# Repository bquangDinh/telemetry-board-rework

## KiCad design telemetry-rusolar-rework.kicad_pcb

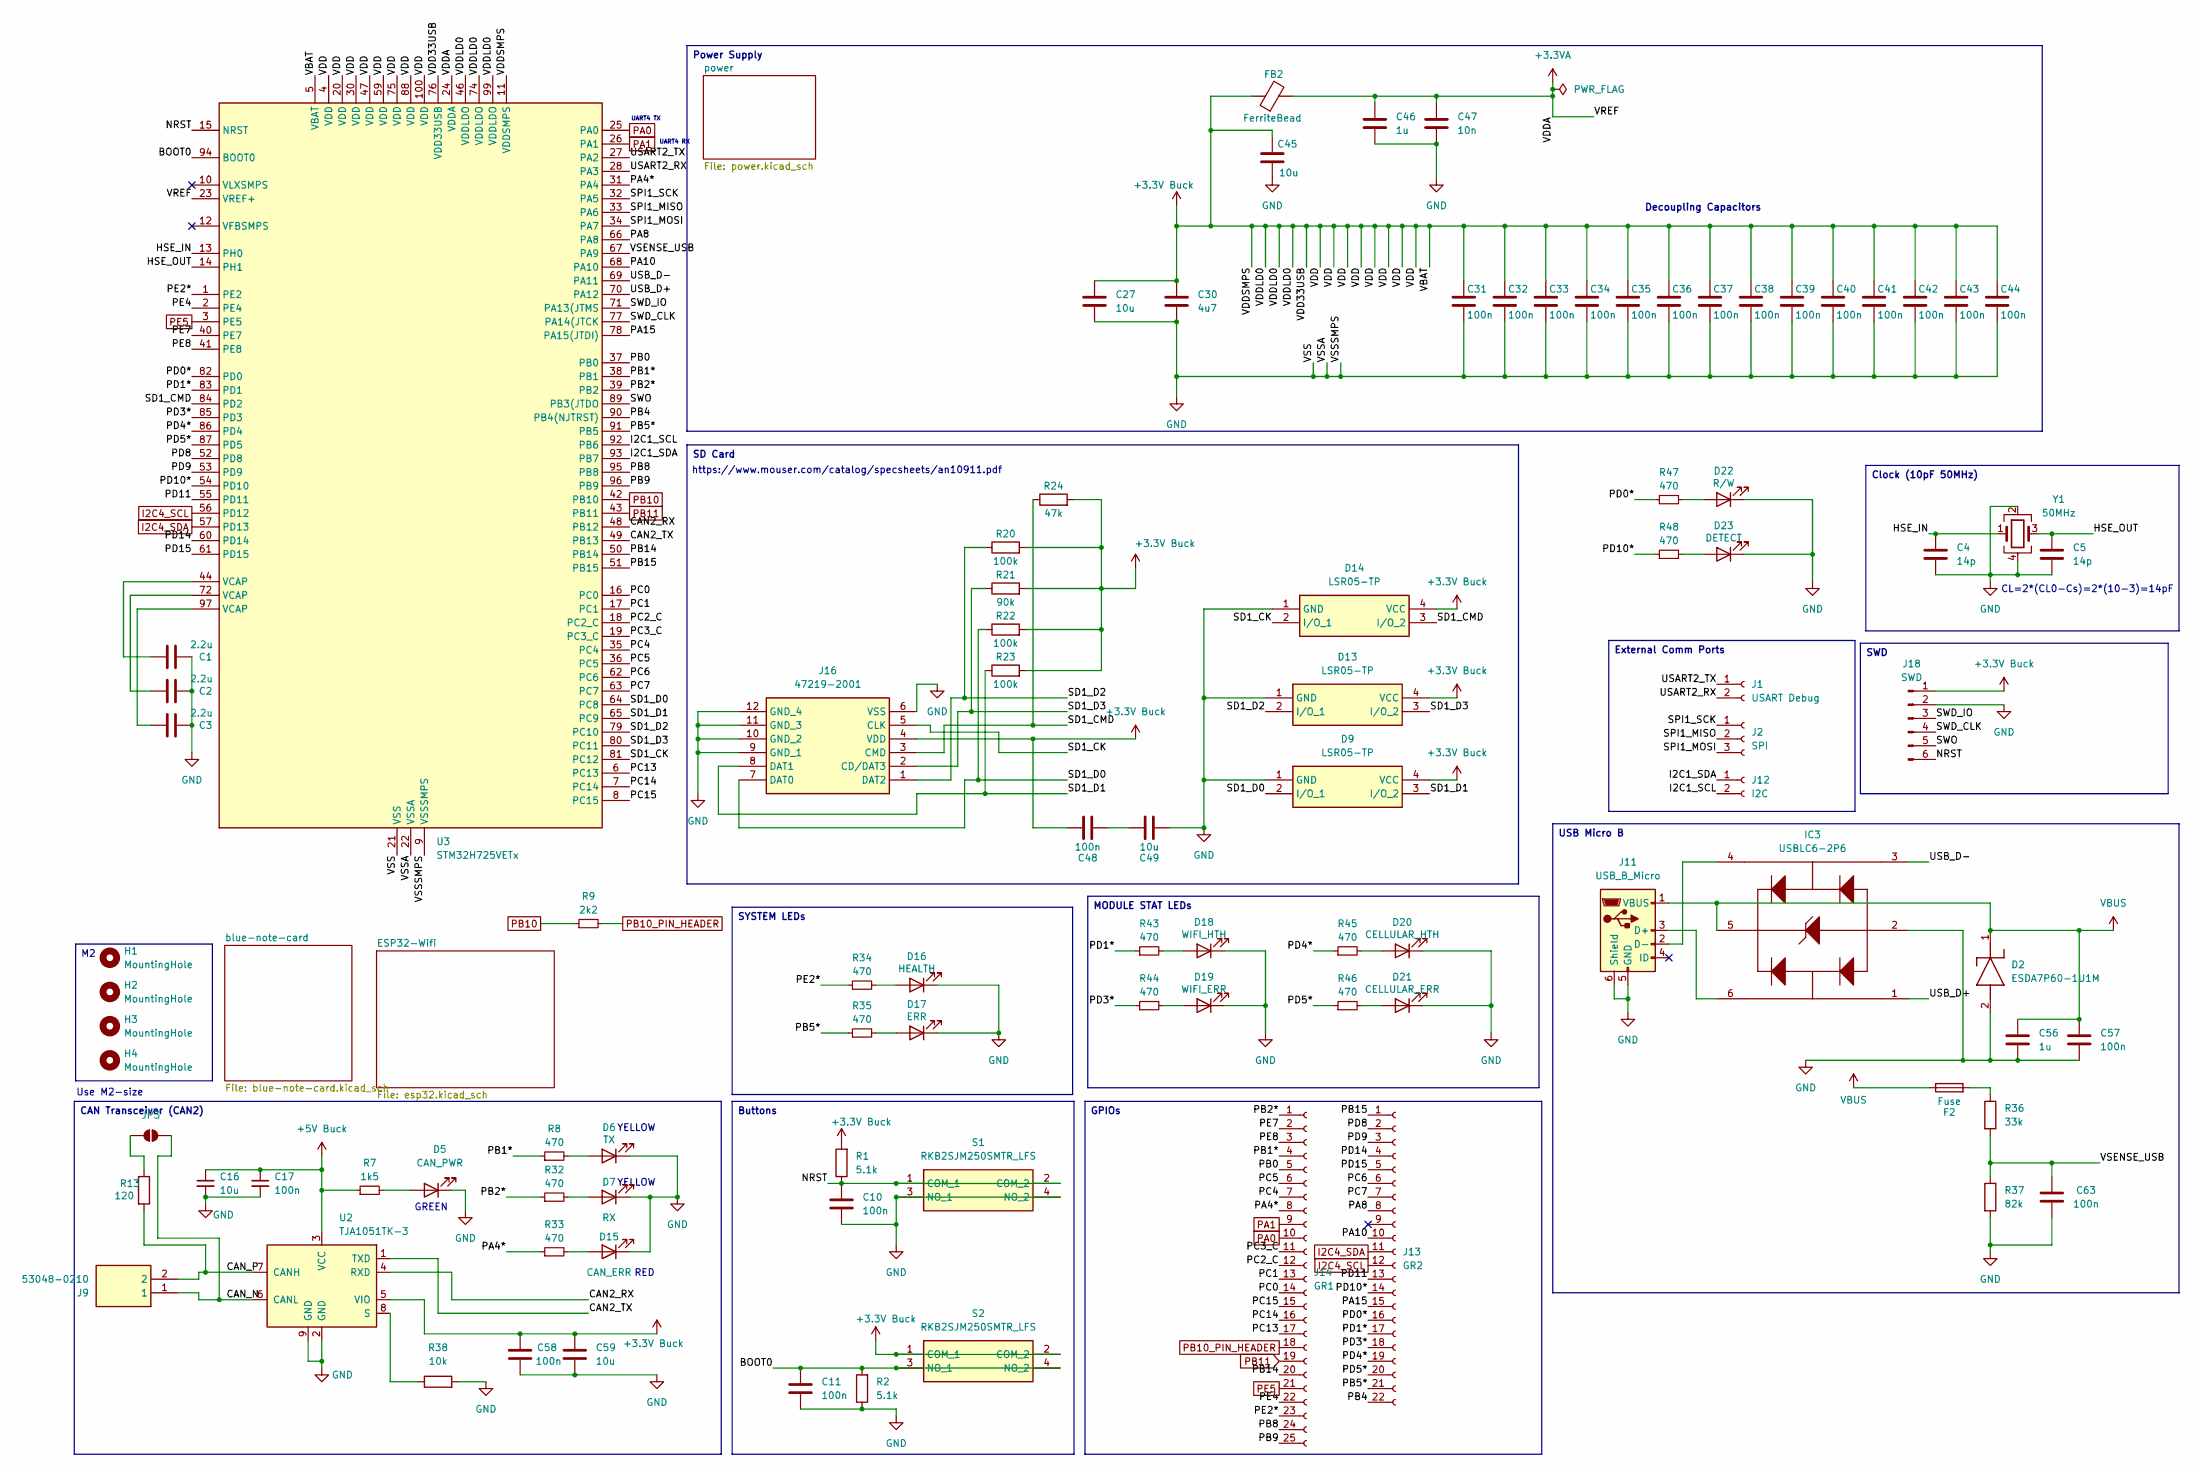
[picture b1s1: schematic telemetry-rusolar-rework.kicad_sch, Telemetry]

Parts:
C1, C2, C3: 2.2u; C_0805_2012Metric_Pad1.18x1.45mm_HandSolder
C4, C5: 14p; C_0603_1608Metric_Pad1.08x0.95mm_HandSolder
C10, C11, C17, C31, C32, C33, C34, C35, C36, C37, C38, C39, C40, C41, C42, C43, C44, C48, C57, C58, C63: 100n; C_0603_1608Metric_Pad1.08x0.95mm_HandSolder
C16, C27, C45, C49, C59: 10u; C_0805_2012Metric_Pad1.18x1.45mm_HandSolder
C30: 4u7; C_0805_2012Metric_Pad1.18x1.45mm_HandSolder
C46, C56: 1u; C_0805_2012Metric_Pad1.18x1.45mm_HandSolder
C47: 10n; C_0603_1608Metric_Pad1.08x0.95mm_HandSolder
D2: ESDA7P60-1U1M; ESDA7P601U1M; Mouser Part Number 511-ESDA7P60-1U1M
D5: CAN_PWR; LED_0805_2012Metric_Pad1.15x1.40mm_HandSolder
D6: TX; LED_0805_2012Metric_Pad1.15x1.40mm_HandSolder
D7: RX; LED_0805_2012Metric_Pad1.15x1.40mm_HandSolder
D9, D13, D14: LSR05-TP; LSR05TP; Mouser Part Number 833-LSR05-TP
D15: CAN_ERR; LED_0805_2012Metric_Pad1.15x1.40mm_HandSolder
D16: HEALTH; LED_0805_2012Metric_Pad1.15x1.40mm_HandSolder
D17: ERR; LED_0805_2012Metric_Pad1.15x1.40mm_HandSolder
D18: WIFI_HTH; LED_0805_2012Metric_Pad1.15x1.40mm_HandSolder
D19: WIFI_ERR; LED_0805_2012Metric_Pad1.15x1.40mm_HandSolder
D20: CELLULAR_HTH; LED_0805_2012Metric_Pad1.15x1.40mm_HandSolder
D21: CELLULAR_ERR; LED_0805_2012Metric_Pad1.15x1.40mm_HandSolder
D22: R/W; LED_0805_2012Metric_Pad1.15x1.40mm_HandSolder
D23: DETECT; LED_0805_2012Metric_Pad1.15x1.40mm_HandSolder
F2: Fuse; Fuse_0603_1608Metric_Pad1.05x0.95mm_HandSolder
FB2: FerriteBead; L_0805_2012Metric_Pad1.15x1.40mm_HandSolder
H1, H2, H3, H4: MountingHole; MountingHole_2.2mm_M2
IC3: USBLC6-2P6; USBLC62P6; Mouser Part Number 511-USBLC6-2P6
J1: USART Debug; PinHeader_1x02_P2.00mm_Vertical
J2: SPI; PinHeader_1x03_P2.00mm_Vertical
J9: 53048-0210; SHDRRA2W35P0X125_1X2_425X550X350P; Mouser Part Number 538-53048-0210
J11: USB_B_Micro; USB_Micro-B_Wuerth_629105150521
J12: I2C; PinHeader_1x02_P2.00mm_Vertical
J13: GR2; PinSocket_1x22_P2.00mm_Vertical
J14: GR1; PinSocket_1x25_P2.00mm_Vertical
J16: 47219-2001; 472192001; Mouser Part Number 538-47219-2001
J18: SWD; PinHeader_1x06_P2.00mm_Vertical
JP3: SolderJumper_2_Open; SolderJumper-2_P1.3mm_Open_RoundedPad1.0x1.5mm
R1, R2: 5.1k; R_0603_1608Metric_Pad0.98x0.95mm_HandSolder
R7: 1k5; R_0603_1608Metric_Pad0.98x0.95mm_HandSolder
R8, R32, R33, R34, R35, R43, R44, R45, R46, R47, R48: 470; R_0603_1608Metric_Pad0.98x0.95mm_HandSolder
R9: 2k2; R_0603_1608Metric_Pad0.98x0.95mm_HandSolder
R13: 120; R_0603_1608Metric_Pad0.98x0.95mm_HandSolder
R20, R22, R23: 100k; R_0805_2012Metric_Pad1.20x1.40mm_HandSolder
R21: 90k; R_0805_2012Metric_Pad1.20x1.40mm_HandSolder
R24: 47k; R_0805_2012Metric_Pad1.20x1.40mm_HandSolder
R36: 33k; R_0603_1608Metric_Pad0.98x0.95mm_HandSolder
R37: 82k; R_0603_1608Metric_Pad0.98x0.95mm_HandSolder
R38: 10k; R_0603_1608Metric_Pad0.98x0.95mm_HandSolder
S1, S2: RKB2SJM250SMTR_LFS; RKB2SJM250SMTRLFS; Mouser Part Number 611-RKB2SJM250SMTRLF
U2: TJA1051TK-3; DFN-8-1EP_3x3mm_P0.65mm_EP1.55x2.4mm
U3: STM32H725VETx; LQFP-100_14x14mm_P0.5mm
Y1: 50MHz; Crystal_SMD_3225-4Pin_3.2x2.5mm

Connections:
+3.3V Buck: C27.2, C30.2, C31.1, C32.1, C33.1, C34.1, C35.1, C36.1, C37.1, C38.1, C39.1, C40.1, C41.1, C42.1, C43.1, C44.1, C45.2, C48.1, C58.2, C59.2, D9.4 (VCC), D13.4 (VCC), D14.4 (VCC), FB2.1, J16.4 (VDD), J18.1, R1.2, R20.2, R21.2, R22.2, R23.2, R24.2, S2.1 (COM_1), S2.2 (COM_2), U2.5 (VIO), U3.4 (VDD), U3.5 (VBAT), U3.11 (VDDSMPS), U3.20 (VDD), U3.30 (VDD), U3.46 (VDDLDO), U3.47 (VDD), U3.59 (VDD), U3.74 (VDDLDO), U3.75 (VDD), U3.76 (VDD33USB), U3.88 (VDD), U3.99 (VDDLDO), U3.100 (VDD); also elsewhere on the board
+3.3VA: C46.2, C47.2, FB2.2, U3.23 (VREF+), U3.24 (VDDA)
+5V Buck: C16.1, C17.1, R7.1, U2.3 (VCC); also elsewhere on the board
/BOOT0: C11.1, R2.2, S2.3 (NO_1), S2.4 (NO_2), U3.94 (BOOT0)
/CAN2_RX: U2.4 (RXD), U3.48 (PB12)
/CAN2_TX: U2.1 (TXD), U3.49 (PB13)
/CAN_N: J9.1, JP3.2 (B), U2.6 (CANL)
/CAN_P: J9.2, R13.2, U2.7 (CANH)
/HSE_IN: C4.1, U3.13 (PH0), Y1.1
/HSE_OUT: C5.1, U3.14 (PH1), Y1.3
/I2C1_SCL: J12.2, U3.92 (PB6)
/I2C1_SDA: J12.1, U3.93 (PB7)
/NRST: C10.1, J18.6, R1.1, S1.1 (COM_1), S1.2 (COM_2), U3.15 (NRST)
/PA4*: J14.8, R33.1, U3.31 (PA4)
/PA8: J13.8, U3.66 (PA8)
/PA10: J13.10, U3.68 (PA10)
/PA15: J13.15, U3.78 (PA15(JTDI))
/PB0: J14.5, U3.37 (PB0)
/PB1*: J14.4, R8.1, U3.38 (PB1)
/PB2*: J14.1, R32.1, U3.39 (PB2)
/PB4: J13.22, U3.90 (PB4(NJTRST))
/PB5*: J13.21, R35.1, U3.91 (PB5)
/PB8: J14.24, U3.95 (PB8)
/PB9: J14.25, U3.96 (PB9)
/PB14: J14.20, U3.50 (PB14)
/PB15: J13.1, U3.51 (PB15)
/PC0: J14.14, U3.16 (PC0)
/PC1: J14.13, U3.17 (PC1)
/PC2_C: J14.12, U3.18 (PC2_C)
/PC3_C: J14.11, U3.19 (PC3_C)
/PC4: J14.7, U3.35 (PC4)
/PC5: J14.6, U3.36 (PC5)
/PC6: J13.6, U3.62 (PC6)
/PC7: J13.7, U3.63 (PC7)
/PC13: J14.17, U3.6 (PC13)
/PC14: J14.16, U3.7 (PC14)
/PC15: J14.15, U3.8 (PC15)
/PD0*: J13.16, R47.1, U3.82 (PD0)
/PD1*: J13.17, R43.1, U3.83 (PD1)
/PD3*: J13.18, R44.1, U3.85 (PD3)
/PD4*: J13.19, R45.1, U3.86 (PD4)
/PD5*: J13.20, R46.1, U3.87 (PD5)
/PD8: J13.2, U3.52 (PD8)
/PD9: J13.3, U3.53 (PD9)
/PD10*: J13.14, R48.1, U3.54 (PD10)
/PD11: J13.13, U3.55 (PD11)
/PD14: J13.4, U3.60 (PD14)
/PD15: J13.5, U3.61 (PD15)
/PE2*: J14.23, R34.1, U3.1 (PE2)
/PE4: J14.22, U3.2 (PE4)
/PE7: J14.2, U3.40 (PE7)
/PE8: J14.3, U3.41 (PE8)
/SD1_CK: D14.2 (I/O_1), J16.5 (CLK), U3.81 (PC12)
/SD1_CMD: D14.3 (I/O_2), J16.3 (CMD), R24.1, U3.84 (PD2)
/SD1_D0: D9.2 (I/O_1), J16.7 (DAT0), R22.1, U3.64 (PC8)
/SD1_D1: D9.3 (I/O_2), J16.8 (DAT1), R23.1, U3.65 (PC9)
/SD1_D2: D13.2 (I/O_1), J16.1 (DAT2), R20.1, U3.79 (PC10)
/SD1_D3: D13.3 (I/O_2), J16.2 (CD/DAT3), R21.1, U3.80 (PC11)
/SPI1_MISO: J2.2, U3.33 (PA6)
/SPI1_MOSI: J2.3, U3.34 (PA7)
/SPI1_SCK: J2.1, U3.32 (PA5)
/SWD_CLK: J18.4, U3.77 (PA14(JTCK)
/SWD_IO: J18.3, U3.71 (PA13(JTMS)
/SWO: J18.5, U3.89 (PB3(JTDO)
/USART2_RX: J1.2, U3.28 (PA3)
/USART2_TX: J1.1, U3.27 (PA2)
/USB_D+: IC3.1 (I/O1_1), U3.70 (PA12)
/USB_D-: IC3.3 (I/O2_1), U3.69 (PA11)
/VSENSE_USB: C63.1, R36.2, R37.1, U3.67 (PA9)
GND: C1.1, C2.1, C3.1, C4.2, C5.2, C10.2, C11.2, C16.2, C17.2, C27.1, C30.1, C31.2, C32.2, C33.2, C34.2, C35.2, C36.2, C37.2, C38.2, C39.2, C40.2, C41.2, C42.2, C43.2, C44.2, C45.1, C46.1, C47.1, C49.2, C56.2, C57.2, C58.1, C59.1, C63.2, D2.2 (A), D5.1 (K), D6.1 (K), D7.1 (K), D9.1 (GND), D13.1 (GND), D14.1 (GND), D15.1 (K), D16.1 (K), D17.1 (K), D18.1 (K), D19.1 (K), D20.1 (K), D21.1 (K), D22.1 (K), D23.1 (K), IC3.2 (GND), J11.5 (GND), J11.6 (Shield), J16.6 (VSS), J16.9 (GND_1), J16.10 (GND_2), J16.11 (GND_3), J16.12 (GND_4), J18.2, R2.1, R37.2, R38.2, S1.3 (NO_1), S1.4 (NO_2), U2.2 (GND), U2.9 (GND), U3.9 (VSSSMPS), U3.21 (VSS), U3.22 (VSSA), U3.29 (VSS), U3.45 (VSS), U3.58 (VSS), U3.73 (VSS), U3.98 (VSS), Y1.2, Y1.4; also elsewhere on the board
I2C4_SCL: J13.12, U3.56 (PD12); also elsewhere on the board
I2C4_SDA: J13.11, U3.57 (PD13); also elsewhere on the board
unnamed: C1.2, U3.44 (VCAP)
unnamed: C2.2, U3.72 (VCAP)
unnamed: C3.2, U3.97 (VCAP)
unnamed: C48.2, C49.1
unnamed: D5.2 (A), R7.2
unnamed: D6.2 (A), R8.2
unnamed: D7.2 (A), R32.2
unnamed: D15.2 (A), R33.2
unnamed: D16.2 (A), R34.2
unnamed: D17.2 (A), R35.2
unnamed: D18.2 (A), R43.2
unnamed: D19.2 (A), R44.2
unnamed: D20.2 (A), R45.2
unnamed: D21.2 (A), R46.2
unnamed: D22.2 (A), R47.2
unnamed: D23.2 (A), R48.2
unnamed: F2.2, R36.1
unnamed: IC3.6 (I/O1_2), J11.3 (D+)
unnamed: IC3.4 (I/O2_2), J11.2 (D-)
unnamed: JP3.1 (A), R13.1
unnamed: R38.1, U2.8 (S)
PA0: J14.10, U3.25 (PA0); also elsewhere on the board
PA1: J14.9, U3.26 (PA1); also elsewhere on the board
PB10: R9.1, U3.42 (PB10)
PB10_PIN_HEADER: J14.18, R9.2; also elsewhere on the board
PB11: J14.19, U3.43 (PB11); also elsewhere on the board
PE5: J14.21, U3.3 (PE5); also elsewhere on the board
VBUS: C56.1, C57.1, D2.1 (K), F2.1, IC3.5 (VBUS), J11.1 (VBUS)

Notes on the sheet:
RED
UART4 TX
https://www.mouser.com/catalog/specsheets/an10911.pdf
Use M2-size
GREEN
CL=2*(CL0-Cs)=2*(10-3)=14pF
UART4 RX
YELLOW
Decoupling Capacitors
SD Card
Buttons
SYSTEM LEDs
Clock (10pF 50MHz)
Power Supply
MODULE STAT LEDs
SWD
USB Micro B
GPIOs
CAN Transceiver (CAN2)
External Comm Ports

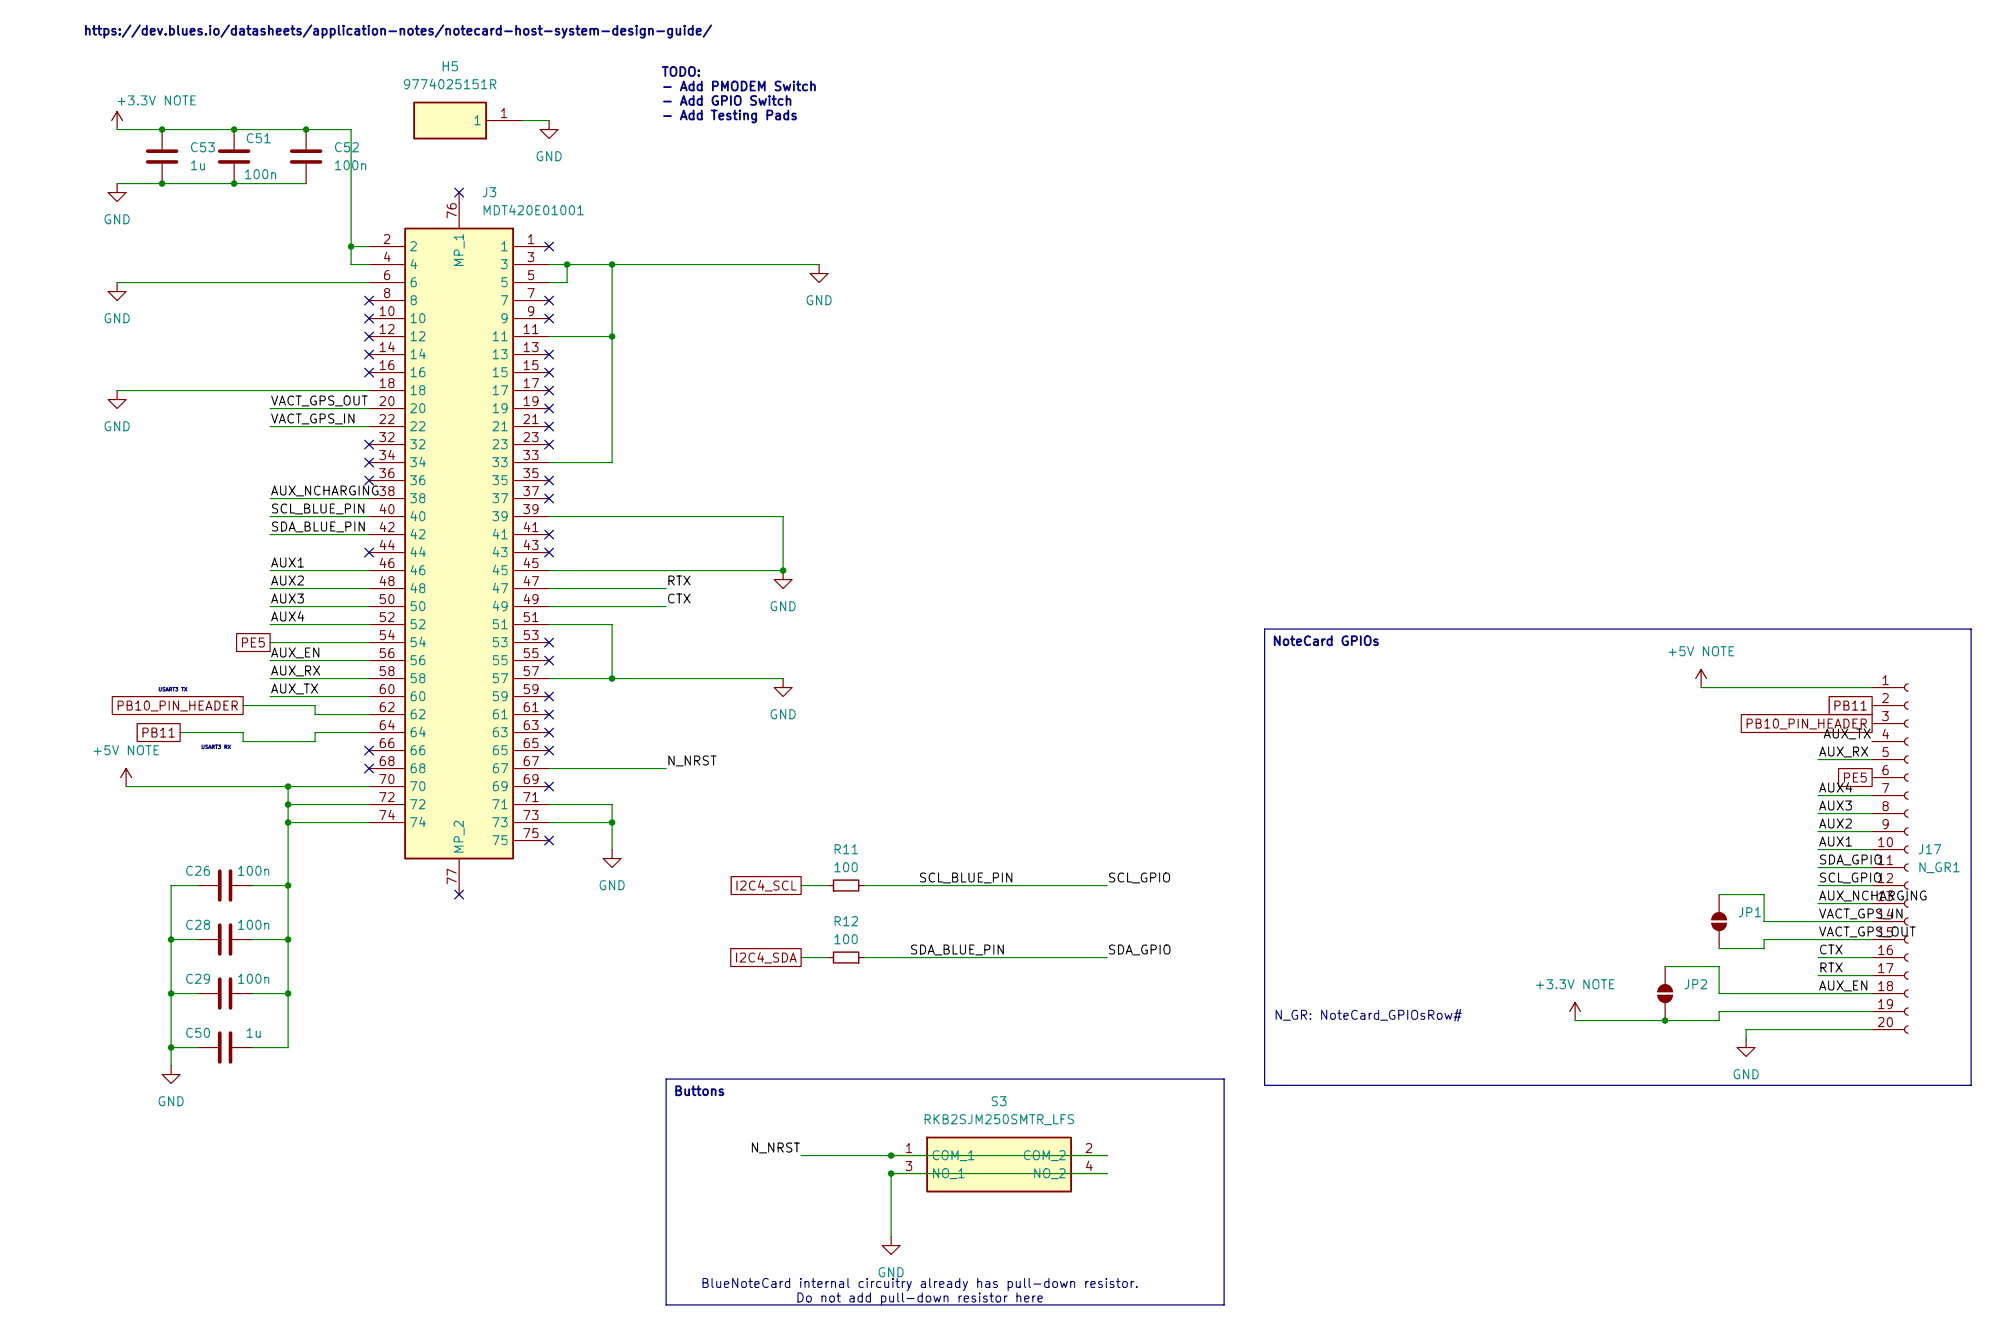
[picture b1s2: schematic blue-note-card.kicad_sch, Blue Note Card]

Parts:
C26, C28, C29, C51, C52: 100n; C_0603_1608Metric_Pad1.08x0.95mm_HandSolder
C50, C53: 1u; C_0805_2012Metric_Pad1.18x1.45mm_HandSolder
H5: 9774025151R; Mouser Part Number 710-9774025151R
J3: MDT420E01001; Mouser Part Number 523-MDT420E01001
J17: N_GR1; PinSocket_1x20_P2.00mm_Vertical
JP1, JP2: SolderJumper_2_Open; SolderJumper-2_P1.3mm_Open_RoundedPad1.0x1.5mm
R11, R12: 100; R_0603_1608Metric_Pad0.98x0.95mm_HandSolder
S3: RKB2SJM250SMTR_LFS; RKB2SJM250SMTRLFS; Mouser Part Number 611-RKB2SJM250SMTRLF

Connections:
+3.3V NOTE: C51.2, C52.2, C53.2, J3.2, J3.4, J17.19, JP2.2 (B); also elsewhere on the board
+5V NOTE: C26.2, C28.2, C29.2, C50.2, J3.70, J3.72, J3.74, J17.1; also elsewhere on the board
/blue-note-card/AUX1: J3.46, J17.10
/blue-note-card/AUX2: J3.48, J17.9
/blue-note-card/AUX3: J3.50, J17.8
/blue-note-card/AUX4: J3.52, J17.7
/blue-note-card/AUX_EN: J3.56, J17.18, JP2.1 (A)
/blue-note-card/AUX_NCHARGING: J3.38, J17.13
/blue-note-card/AUX_RX: J3.58, J17.5
/blue-note-card/AUX_TX: J3.60, J17.4
/blue-note-card/CTX: J3.49, J17.16
/blue-note-card/N_NRST: J3.67, S3.1 (COM_1), S3.2 (COM_2)
/blue-note-card/RTX: J3.47, J17.17
/blue-note-card/SCL_BLUE_PIN: J3.40, J17.12, R11.2
/blue-note-card/SDA_BLUE_PIN: J3.42, J17.11, R12.1
/blue-note-card/VACT_GPS_IN: J3.22, J17.14, JP1.1 (A)
/blue-note-card/VACT_GPS_OUT: J3.20, J17.15, JP1.2 (B)
GND: C26.1, C28.1, C29.1, C50.1, C51.1, C52.1, C53.1, H5.1, J3.3, J3.5, J3.6, J3.11, J3.18, J3.33, J3.39, J3.45, J3.51, J3.57, J3.71, J3.73, J17.20, S3.3 (NO_1), S3.4 (NO_2); also elsewhere on the board
I2C4_SCL: R11.1; also elsewhere on the board
I2C4_SDA: R12.2; also elsewhere on the board
PB10_PIN_HEADER: J3.62, J17.3; also elsewhere on the board
PB11: J3.64, J17.2; also elsewhere on the board
PE5: J3.54, J17.6; also elsewhere on the board

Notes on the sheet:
TODO: - Add PMODEM Switch - Add GPIO Switch - Add Testing Pads
BlueNoteCard internal circuitry already has pull-down resistor. Do not add pull-down resistor here
https://dev.blues.io/datasheets/application-notes/notecard-host-system-design-guide/
N_GR: NoteCard_GPIOsRow#
USART3 RX
USART3 TX
Buttons
NoteCard GPIOs

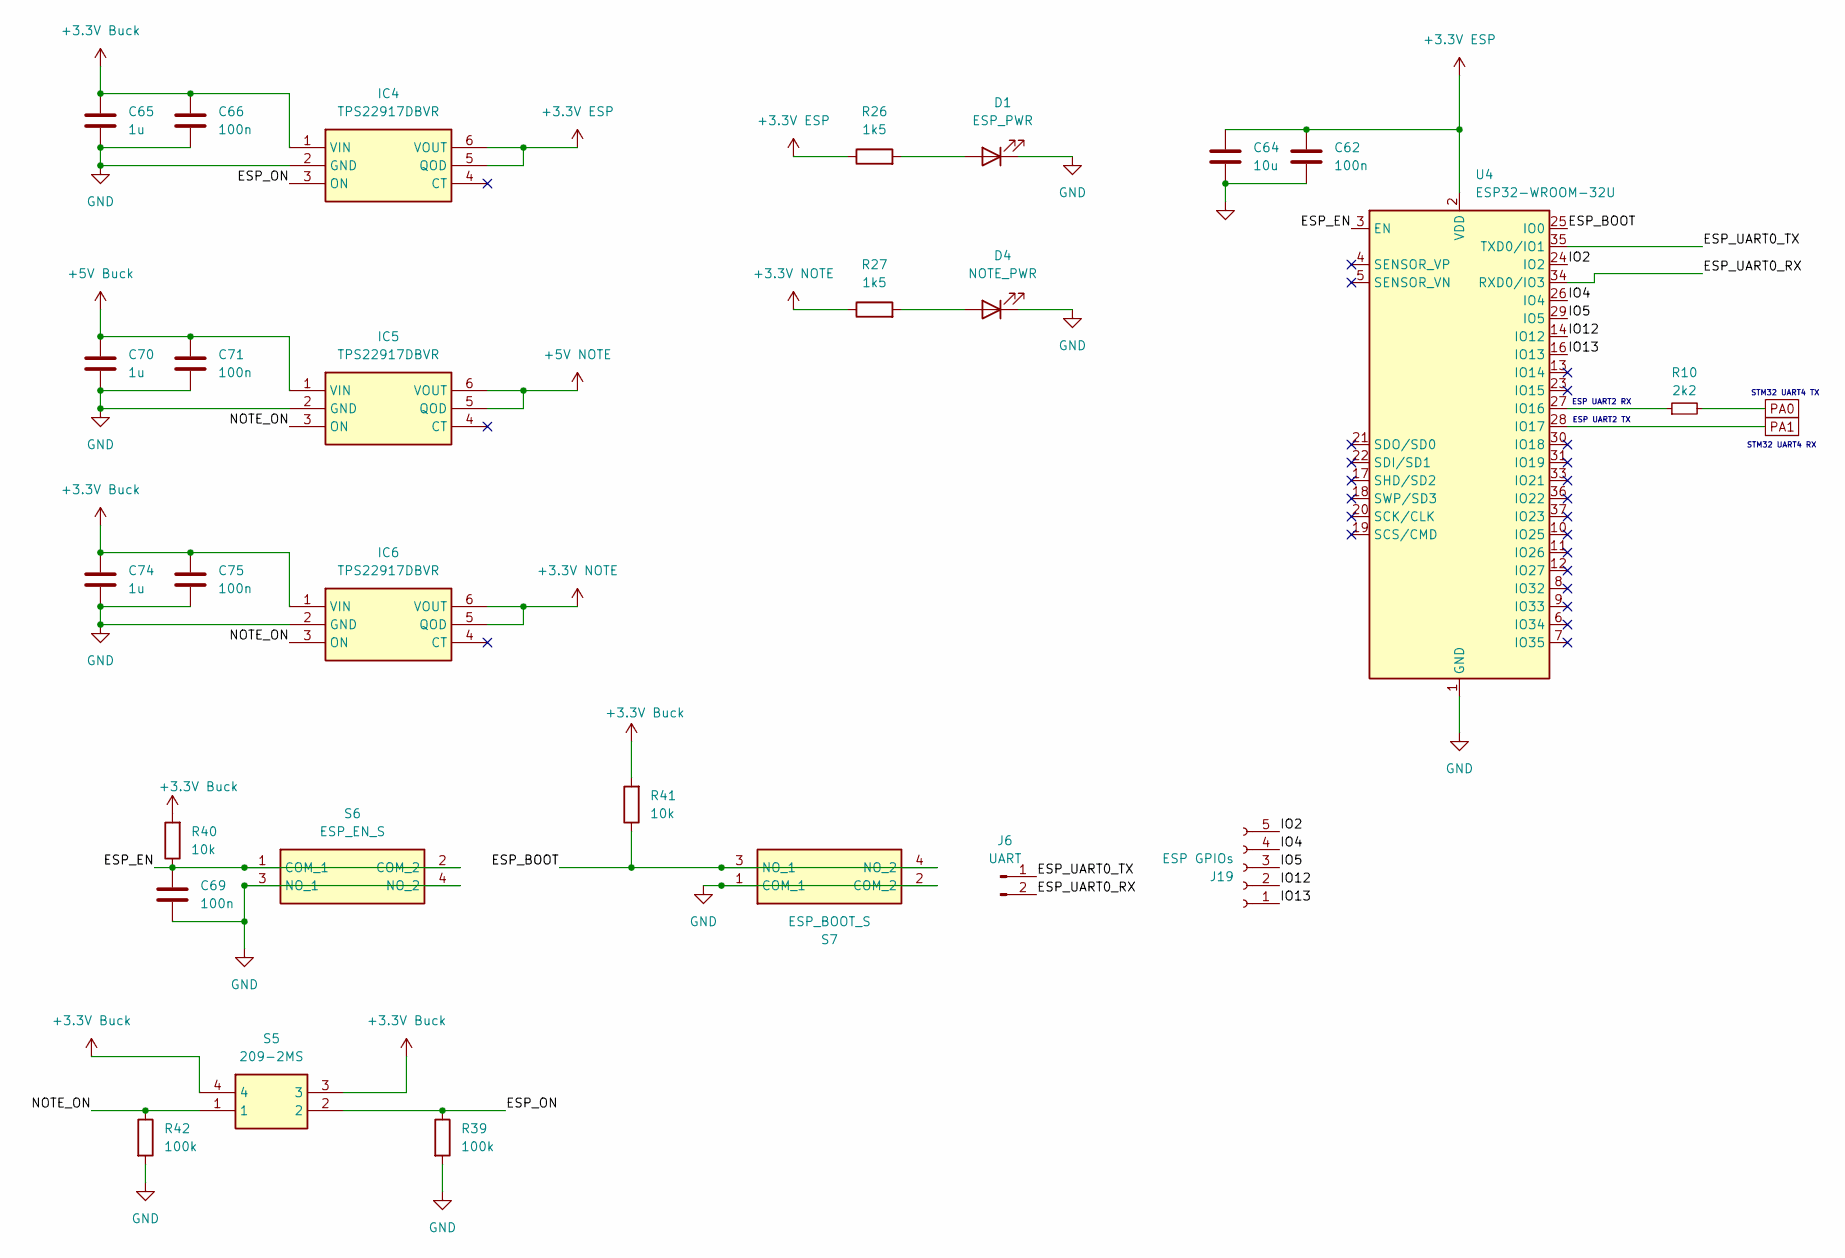
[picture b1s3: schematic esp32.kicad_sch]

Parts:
C62, C66, C69, C71, C75: 100n; C_0603_1608Metric_Pad1.08x0.95mm_HandSolder
C64: 10u; C_0805_2012Metric_Pad1.18x1.45mm_HandSolder
C65, C70, C74: 1u; C_0805_2012Metric_Pad1.18x1.45mm_HandSolder
D1: ESP_PWR; LED_0805_2012Metric_Pad1.15x1.40mm_HandSolder
D4: NOTE_PWR; LED_0805_2012Metric_Pad1.15x1.40mm_HandSolder
IC4, IC5, IC6: TPS22917DBVR; SOT95P280X145-6N; Mouser Part Number 595-TPS22917DBVR
J6: UART; PinHeader_1x02_P2.00mm_Vertical
J19: ESP GPIOs; PinSocket_1x05_P2.00mm_Vertical
R10: 2k2; R_0603_1608Metric_Pad0.98x0.95mm_HandSolder
R26, R27: 1k5; R_0603_1608Metric_Pad0.98x0.95mm_HandSolder
R39, R42: 100k; R_0805_2012Metric_Pad1.20x1.40mm_HandSolder
R40, R41: 10k; R_0603_1608Metric_Pad0.98x0.95mm_HandSolder
S5: 209-2MS; 2092MS; Mouser Part Number 774-2092MS
S6: ESP_EN_S; RKB2SJM250SMTRLFS; Mouser Part Number 611-RKB2SJM250SMTRLF
S7: ESP_BOOT_S; RKB2SJM250SMTRLFS; Mouser Part Number 611-RKB2SJM250SMTRLF
U4: ESP32-WROOM-32U

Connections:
+3.3V Buck: C65.1, C66.1, C74.1, C75.1, IC4.1 (VIN), IC6.1 (VIN), R40.2, R41.2, S5.3, S5.4; also elsewhere on the board
+3.3V ESP: C62.1, C64.1, IC4.5 (QOD), IC4.6 (VOUT), R26.1, U4.2 (VDD)
+3.3V NOTE: IC6.5 (QOD), IC6.6 (VOUT), R27.1; also elsewhere on the board
+5V Buck: C70.1, C71.1, IC5.1 (VIN); also elsewhere on the board
+5V NOTE: IC5.5 (QOD), IC5.6 (VOUT); also elsewhere on the board
/ESP32-Wifi/ESP_BOOT: R41.1, S7.3 (NO_1), S7.4 (NO_2), U4.25 (IO0)
/ESP32-Wifi/ESP_EN: C69.1, R40.1, S6.1 (COM_1), S6.2 (COM_2), U4.3 (EN)
/ESP32-Wifi/ESP_ON: IC4.3 (ON), R39.1, S5.2
/ESP32-Wifi/ESP_UART0_RX: J6.2, U4.34 (RXD0/IO3)
/ESP32-Wifi/ESP_UART0_TX: J6.1, U4.35 (TXD0/IO1)
/ESP32-Wifi/IO2: J19.5, U4.24 (IO2)
/ESP32-Wifi/IO4: J19.4, U4.26 (IO4)
/ESP32-Wifi/IO5: J19.3, U4.29 (IO5)
/ESP32-Wifi/IO12: J19.2, U4.14 (IO12)
/ESP32-Wifi/IO13: J19.1, U4.16 (IO13)
/ESP32-Wifi/NOTE_ON: IC5.3 (ON), IC6.3 (ON), R42.1, S5.1
GND: C62.2, C64.2, C65.2, C66.2, C69.2, C70.2, C71.2, C74.2, C75.2, D1.1 (K), D4.1 (K), IC4.2 (GND), IC5.2 (GND), IC6.2 (GND), R39.2, R42.2, S6.3 (NO_1), S6.4 (NO_2), S7.1 (COM_1), S7.2 (COM_2), U4.1 (GND), U4.15 (GND), U4.38 (GND), U4.39 (GND); also elsewhere on the board
unnamed: D1.2 (A), R26.2
unnamed: D4.2 (A), R27.2
unnamed: R10.1, U4.27 (IO16)
PA0: R10.2; also elsewhere on the board
PA1: U4.28 (IO17); also elsewhere on the board

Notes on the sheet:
STM32 UART4 TX
STM32 UART4 RX
ESP UART2 RX
ESP UART2 TX

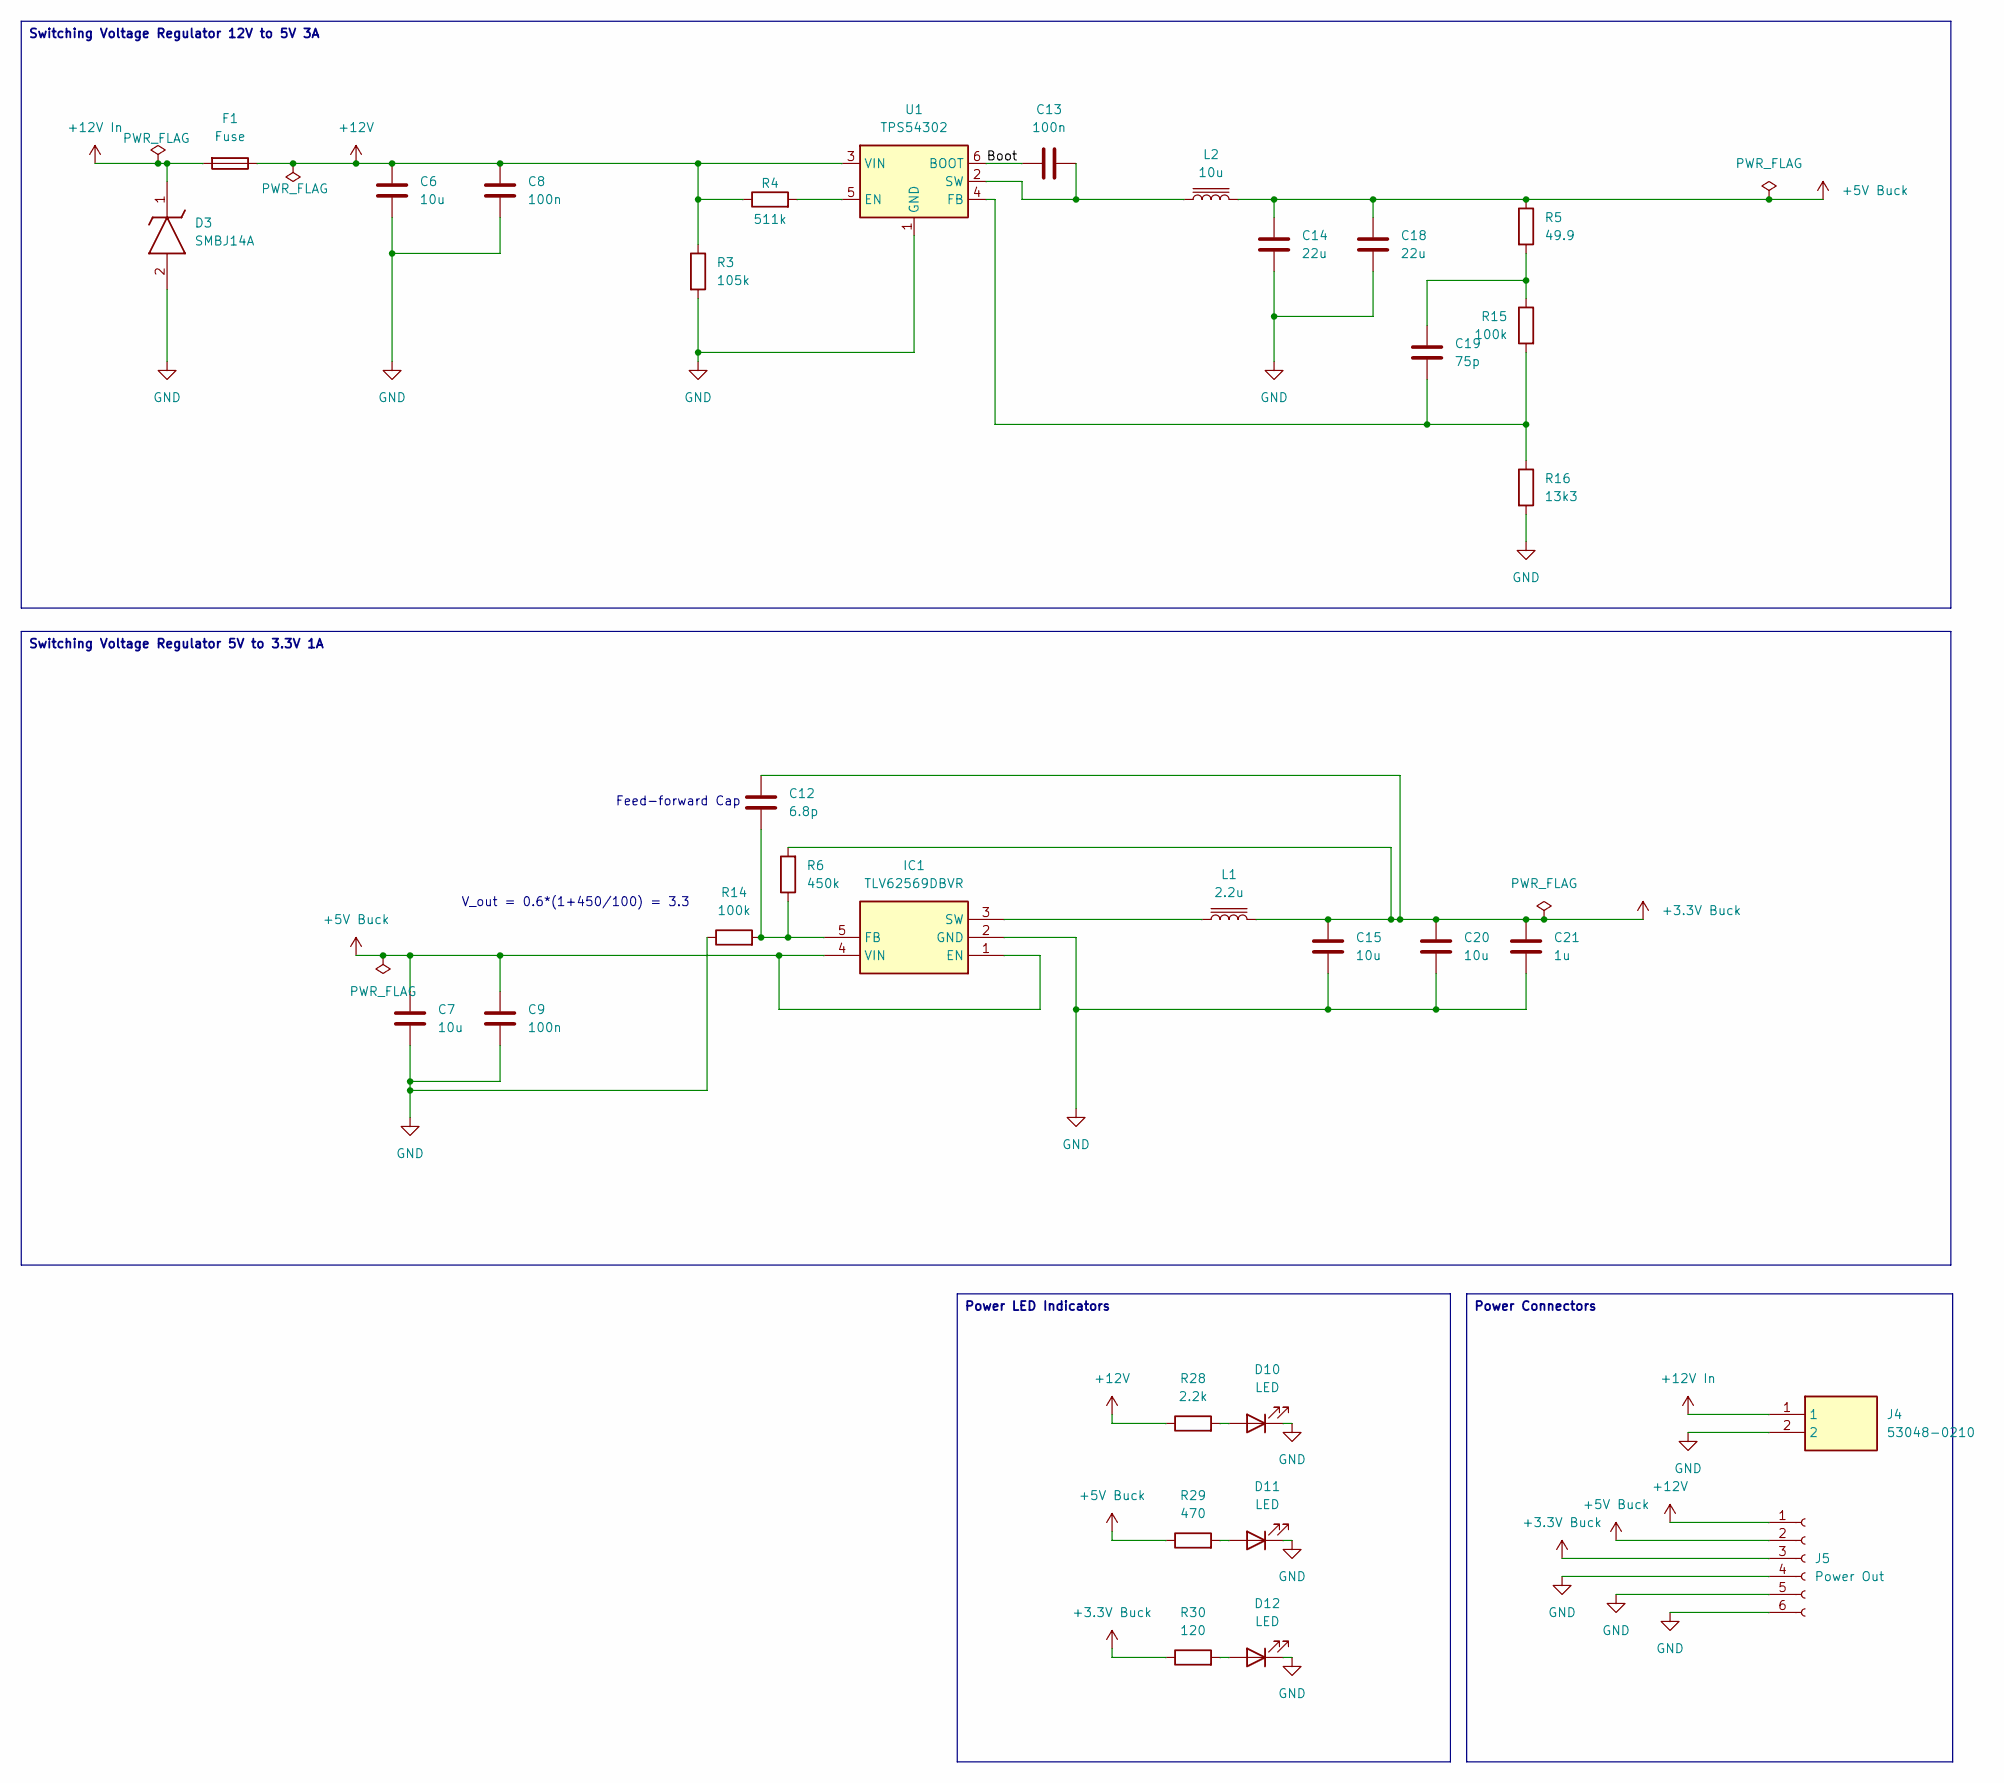
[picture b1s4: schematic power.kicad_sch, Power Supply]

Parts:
C6, C7, C15, C20: 10u; C_0805_2012Metric_Pad1.18x1.45mm_HandSolder
C8, C9, C13: 100n; C_0603_1608Metric_Pad1.08x0.95mm_HandSolder
C12: 6.8p; C_0805_2012Metric_Pad1.18x1.45mm_HandSolder
C14, C18: 22u; C_1210_3225Metric_Pad1.33x2.70mm_HandSolder
C19: 75p; C_0603_1608Metric_Pad1.08x0.95mm_HandSolder
C21: 1u; C_0805_2012Metric_Pad1.18x1.45mm_HandSolder
D3: SMBJ14A; DIOM5436X261N; Mouser Part Number 576-SMBJ14A
D10, D11, D12: LED; LED_0805_2012Metric_Pad1.15x1.40mm_HandSolder
F1: Fuse; Fuseholder_Blade_Mini_Keystone_3568
IC1: TLV62569DBVR; SOT95P280X145-5N; Mouser Part Number 595-TLV62569DBVR
J4: 53048-0210; SHDRRA2W35P0X125_1X2_425X550X350P; Mouser Part Number 538-53048-0210
J5: Power Out; PinSocket_1x06_P2.00mm_Vertical
L1: 2.2u; LQM2HPZ3R3MJ0B
L2: 10u; INDPM6965X300N
R3: 105k; R_0805_2012Metric_Pad1.20x1.40mm_HandSolder
R4: 511k; R_0805_2012Metric_Pad1.20x1.40mm_HandSolder
R5: 49.9; R_0805_2012Metric_Pad1.20x1.40mm_HandSolder
R6: 450k; R_0805_2012Metric_Pad1.20x1.40mm_HandSolder
R14, R15: 100k; R_0805_2012Metric_Pad1.20x1.40mm_HandSolder
R16: 13k3; R_0805_2012Metric_Pad1.20x1.40mm_HandSolder
R28: 2.2k; R_0603_1608Metric_Pad0.98x0.95mm_HandSolder
R29: 470; R_0603_1608Metric_Pad0.98x0.95mm_HandSolder
R30: 120; R_0603_1608Metric_Pad0.98x0.95mm_HandSolder
U1: TPS54302; SOT-23-6

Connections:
+3.3V Buck: C12.2, C15.1, C20.1, C21.1, J5.3, L1.2, R6.2, R30.1; also elsewhere on the board
+5V Buck: C7.2, C9.1, C14.1, C18.1, IC1.1 (EN), IC1.4 (VIN), J5.2, L2.2, R5.1, R29.1; also elsewhere on the board
+12V: C6.1, C8.1, F1.1, J5.1, R3.1, R4.1, R28.1, U1.3 (VIN)
+12V In: D3.1 (K), F1.2, J4.1
/power/Boot: C13.1, U1.6 (BOOT)
GND: C6.2, C7.1, C8.2, C9.2, C14.2, C15.2, C18.2, C20.2, C21.2, D3.2 (A), D10.1 (K), D11.1 (K), D12.1 (K), IC1.2 (GND), J4.2, J5.4, J5.5, J5.6, R3.2, R14.1, R16.2, U1.1 (GND); also elsewhere on the board
unnamed: C19.1, R5.2, R15.1
unnamed: D10.2 (A), R28.2
unnamed: D11.2 (A), R29.2
unnamed: D12.2 (A), R30.2
unnamed: C12.1, IC1.5 (FB), R6.1, R14.2
unnamed: IC1.3 (SW), L1.1
unnamed: R4.2, U1.5 (EN)
unnamed: C19.2, R15.2, R16.1, U1.4 (FB)
unnamed: C13.2, L2.1, U1.2 (SW)

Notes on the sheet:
Feed-forward Cap
V_out = 0.6*(1+450/100) = 3.3
Power Connectors
Power LED Indicators
Switching Voltage Regulator 5V to 3.3V 1A
Switching Voltage Regulator 12V to 5V 3A

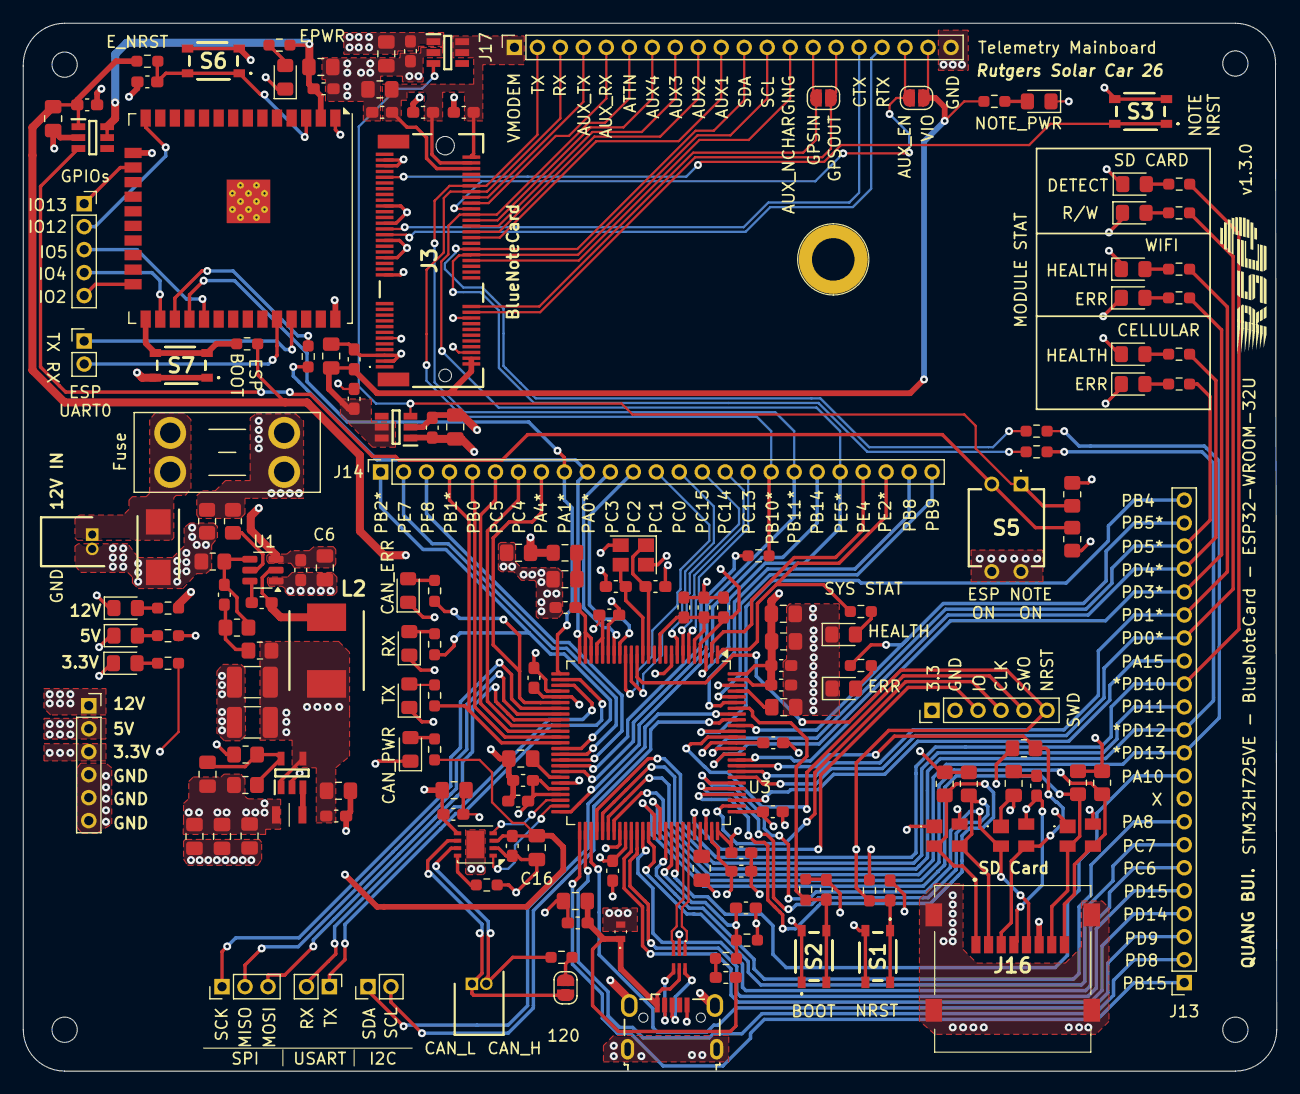
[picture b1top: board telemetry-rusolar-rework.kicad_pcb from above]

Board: 4 copper layers, 109.1 x 91.2 mm, 172 parts (0 on the bottom side), 144 nets.

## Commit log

2025-12-02 Layout parts
2025-12-03 Layout
2025-12-04 Fixed DRC errors
2025-12-04 Added ORing VBUS
2025-12-04 Removed CAN TX/RX LED indicators
2025-12-05 Added LED indicators, USER LEDs, extended layout, fixed footprints
2025-12-05 Relayout NanoSim component
2025-12-16 Added changes
2026-02-15 Fixed USB VSENSE, fixed things
2026-02-17 Fixed things
2026-02-18 Fixed a lot of things
2026-03-14 Added temp
2026-03-25 Changed
2026-03-26 Added AUX_EN, I2C com to Blues, LED labels
2026-03-29 Added module LEDs, I2C for Blues Com
2026-03-29 Fixed SD Card layout
